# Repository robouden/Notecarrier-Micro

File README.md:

# Notecarrier-Micro

This folder contains the design files for the Blues Wireless Notecarrier-Micro, in KiCad 7 format. This is a compact carrier board designed specifically for the Blues Wireless Notecard, providing power management, interface conversion, and mechanical mounting in a minimal form factor.

The Notecarrier-Micro provides essential hardware interfaces including USB-C for programming and power, JST connectors for battery and antenna connections, and standard 0.1" headers for GPIO access. All components are selected for low power consumption and reliability in IoT applications.

## Contents

- This file
 	- `README.md`
- KiCad source files
	- `Notecarrier-Micro.kicad_pcb`
	- `Notecarrier-Micro.kicad_prl`
	- `Notecarrier-Micro.kicad_pro`
	- `Notecarrier-Micro.kicad_sch`
	- `Notecarrier-Micro.kicad_wks`
	- `sym-lib-table`
	- `fp-info-cache`	- `fp-lib-table`
- Documentation	- `documentation/*`
- Manufacturing artefacts
	- `manufacturing/*`
- Design references
	- `reference/*`
- Validation artefacts
	- `validation/*`

## Hardware Specifications

### Physical Characteristics
- **Dimensions**: Compact form factor optimized for space-constrained applications
- **Mounting**: Standard mounting holes for secure installation
- **Connectors**: USB-C, JST battery connector, antenna connectors, 0.1" GPIO headers

### Power Management
- **Input Voltage**: USB-C 5V input, Battery input via JST connector
- **Power Regulation**: On-board voltage regulators for stable 3.3V and other required voltages
- **Low Power Design**: Optimized for battery-powered IoT applications

### Interfaces
- **USB-C**: Programming, debugging, and power input
- **Battery Connector**: JST connector for LiPo battery connection
- **Antenna Connectors**: Standard antenna connections for cellular/WiFi
- **GPIO Headers**: 0.1" pitch headers for external sensor/actuator connections
- **I2C/SPI/UART**: Standard communication interfaces exposed via headers

### Compatibility
- **Notecard Support**: Designed specifically for Blues Wireless Notecard modules
- **Module Interface**: M.2 edge connector for Notecard installation
- **External Access**: All Notecard pins accessible via expansion headers

## Manufacturing Files
- **PCB Files**: Complete KiCad manufacturing package in `manufacturing/` directory
- **3D Models**: STEP and WRL files for mechanical integration
- **Assembly**: Pick and place files, BOM, and assembly drawings

## Revision History

| Revision |    Date    |   Author   | Description |
|:--------:| ---------- | ---------- | ----------- |
|     A    | 2023-03-31 | H.Raftery  | initial port from OrCAD design files, rev 14 (v2.1). |

### Original OrCad Design File Revision History

| Revision |    Date    |   Author   | Description |
|:--------:| ---------- | ---------- | ----------- |
|    12    | 25/08/2020 | G.Boschini | - Changed screw with inox version<br/>- Changed pullup resistor of EN pin to 10M |
|    14    | 25/08/2020 | M. Gregis  | - Added LiPO charger<br/>- Changed V+ to VBAT<br/>- removed BOOT signal from J21 header and replaced with GND<br/>- removed AUX5 from J22 header and replaced with VMODEM |

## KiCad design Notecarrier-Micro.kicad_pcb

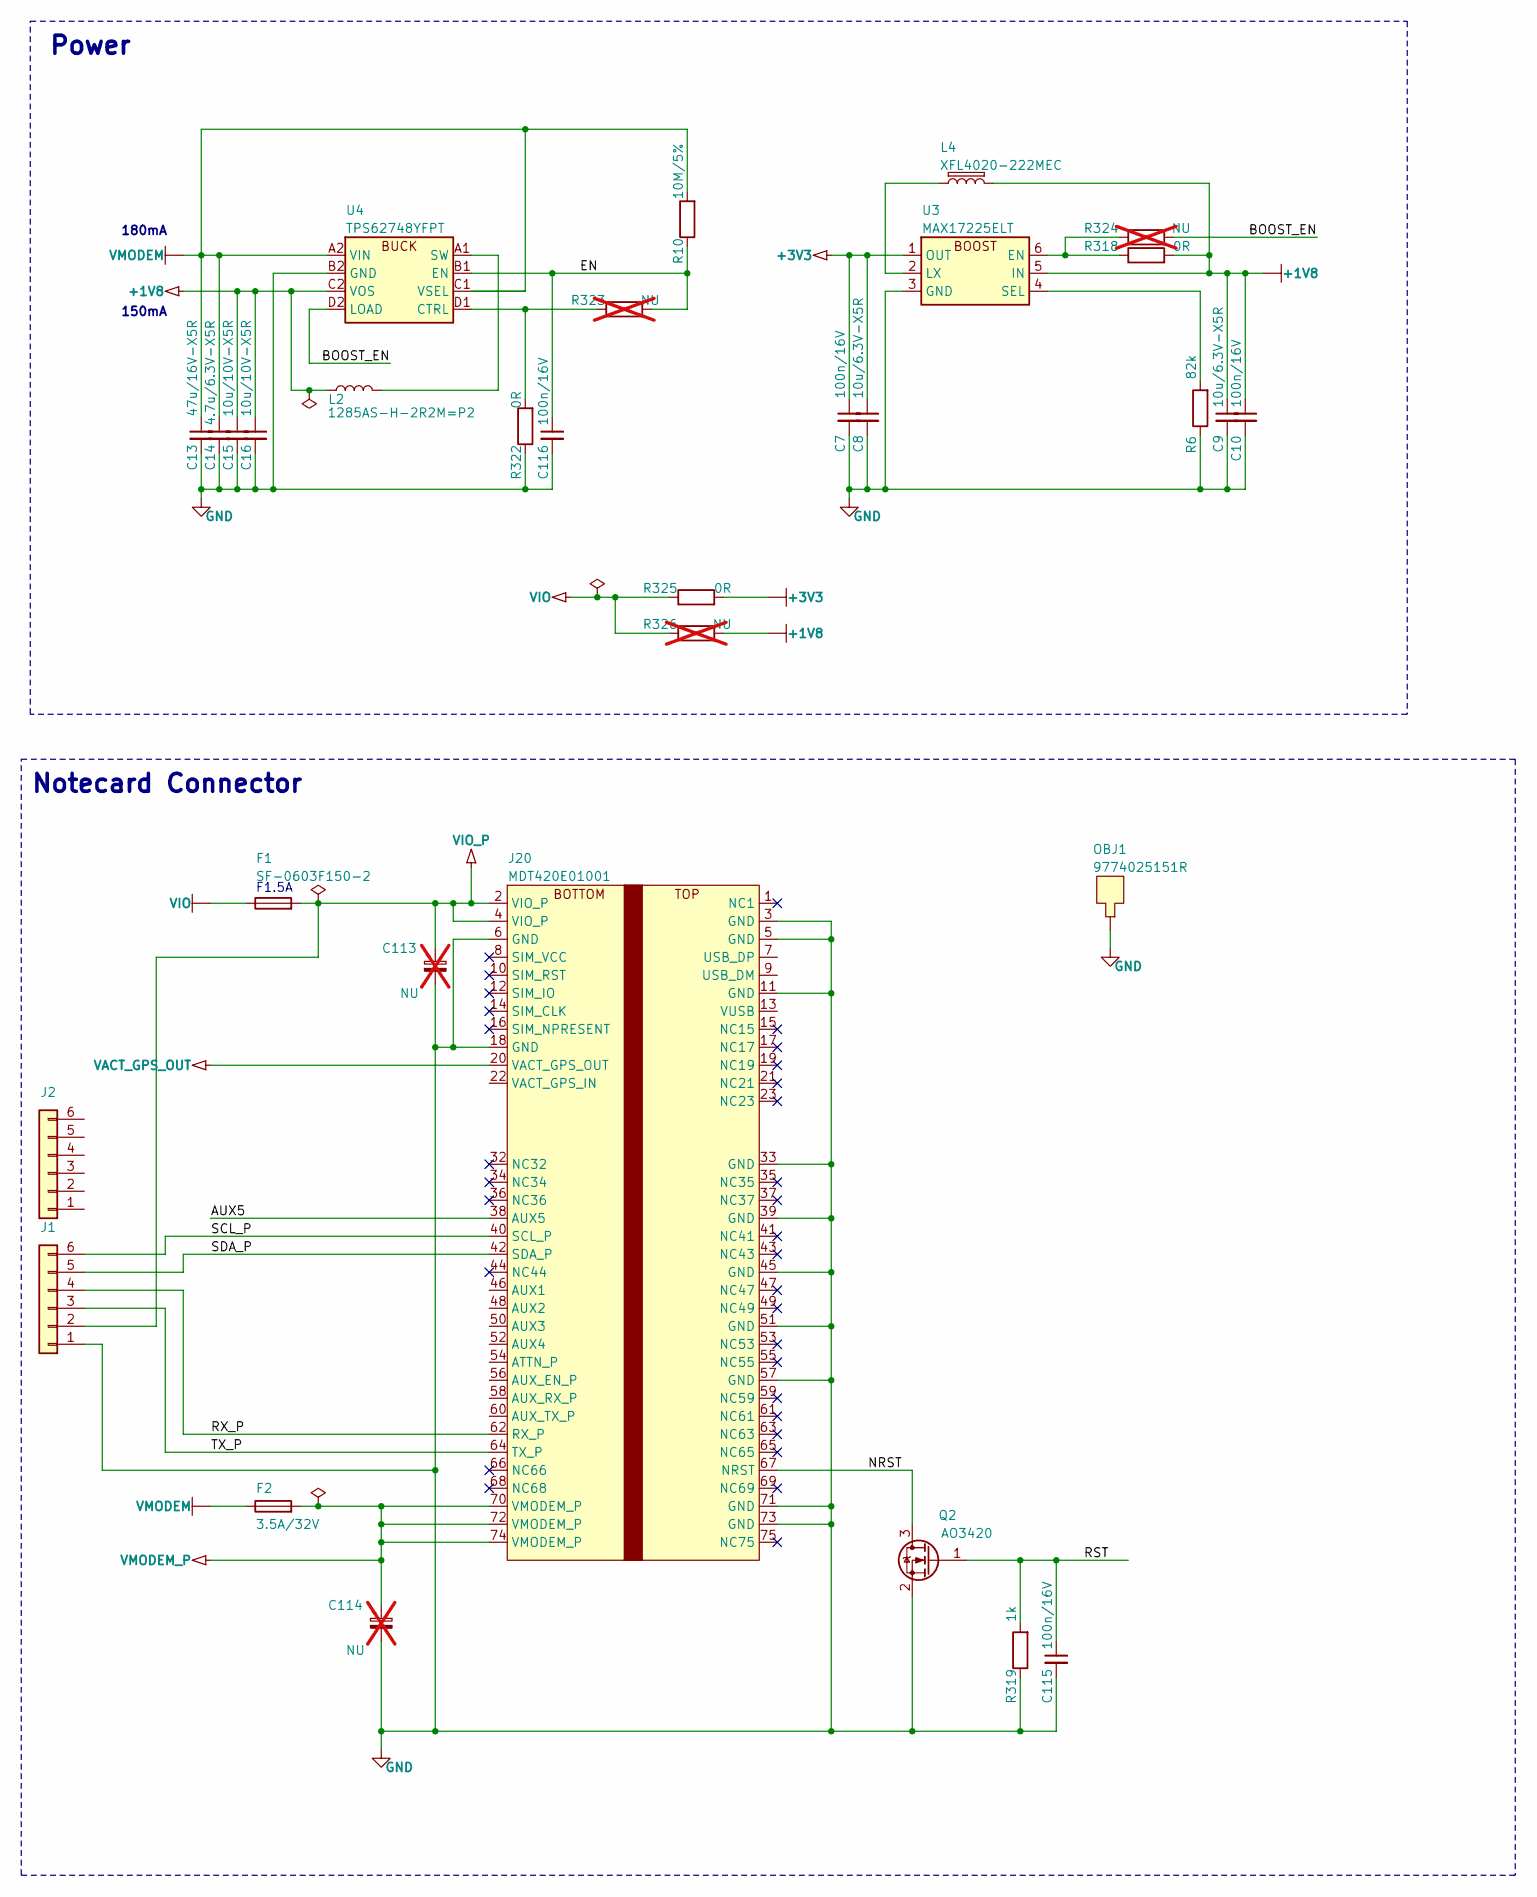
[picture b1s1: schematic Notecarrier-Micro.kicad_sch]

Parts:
C7, C10, C115, C116: 100n/16V; CS-C-0402_NO-FILL
C8, C9: 10u/6.3V-X5R; CS-C-0402_NO-FILL
C13: 47u/16V-X5R; CS-C-1206
C14: 4.7u/6.3V-X5R; CS-C-0402_NO-FILL
C15, C16: 10u/10V-X5R; CS-C-0603
C113: NU; CS-T-A; MPN F930J107KAA; not fitted
C114: NU; CS-T-B; MPN F930J227KBA; not fitted
F1: SF-0603F150-2; FS-0603; MPN SF-0603F150-2
F2: 3.5A/32V; FS-0603; MPN 0603SFV350F/32-2
J1, J2: Conn_01x06; PinHeader_1x06_P2.54mm_Vertical
J20: MDT420E01001; J-75-0050-MOS-M2-E
L2: 1285AS-H-2R2M=P2; LS-0806; MPN 1285AS-H-2R2M=P2
L4: XFL4020-222MEC; LS-XFL4020; MPN XFL4020-222MEC
OBJ1: 9774025151R; DIST-WASMSIM0250
Q2: AO3420; SOT23_NO-FILL
R6: 82k; RS-0402_NO-FILL
R10: 10M/5%; RS-0402_NO-FILL
R318, R322, R325: 0R; RS-0402_NO-FILL
R319: 1k; RS-0402_NO-FILL
R323, R324, R326: NU; RS-0402_NO-FILL; not fitted
U3: MAX17225ELT; WDFN6-0200X0200; MPN MAX17225ELT+T
U4: TPS62748YFPT; XFBGA8; MPN TPS62748YFPT

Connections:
+1V8: C9.1, C10.1, C15.1, C16.1, L2.2, L4.2, R318.2, R326.2, U3.5 (IN), U4.C2 (VOS)
+3V3: C7.1, C8.1, R325.2, U3.1 (OUT)
/AUX5: J20.38 (AUX5)
/BOOST_EN: R324.2, U4.D2 (LOAD)
/EN: C116.1, R10.1, R323.2, U4.B1 (EN)
/NRST: J20.67 (NRST), Q2.3 (D)
/RST: C115.1, Q2.1 (G), R319.2
/RX_P: J1.4, J20.62 (RX_P)
/SCL_P: J1.6, J20.40 (SCL_P)
/SDA_P: J1.5, J20.42 (SDA_P)
/TX_P: J1.3, J20.64 (TX_P)
GND: C7.2, C8.2, C9.2, C10.2, C13.2, C14.2, C15.2, C16.2, C113.2, C114.2, C115.2, C116.2, J1.1, J20.3 (GND), J20.5 (GND), J20.6 (GND), J20.11 (GND), J20.18 (GND), J20.33 (GND), J20.39 (GND), J20.45 (GND), J20.51 (GND), J20.57 (GND), J20.71 (GND), J20.73 (GND), OBJ1.1, Q2.2 (S), R6.1, R319.1, R322.1, U3.3 (GND), U4.B2 (GND)
unnamed: R318.1, R324.1, U3.6 (EN)
unnamed: L4.1, U3.2 (LX)
unnamed: R6.2, U3.4 (SEL)
unnamed: R322.2, R323.1, U4.D1 (CTRL)
unnamed: L2.1, U4.A1 (SW)
VACT_GPS_OUT: J20.20 (VACT_GPS_OUT)
VIO: F1.1, R325.1, R326.1
VIO_P: C113.1, F1.2, J1.2, J20.2 (VIO_P), J20.4 (VIO_P)
VMODEM: C13.1, C14.1, F2.1, R10.2, U4.A2 (VIN), U4.C1 (VSEL)
VMODEM_P: C114.1, F2.2, J20.70 (VMODEM_P), J20.72 (VMODEM_P), J20.74 (VMODEM_P)

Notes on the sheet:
150mA
180mA
F1.5A
Notecard Connector
Power

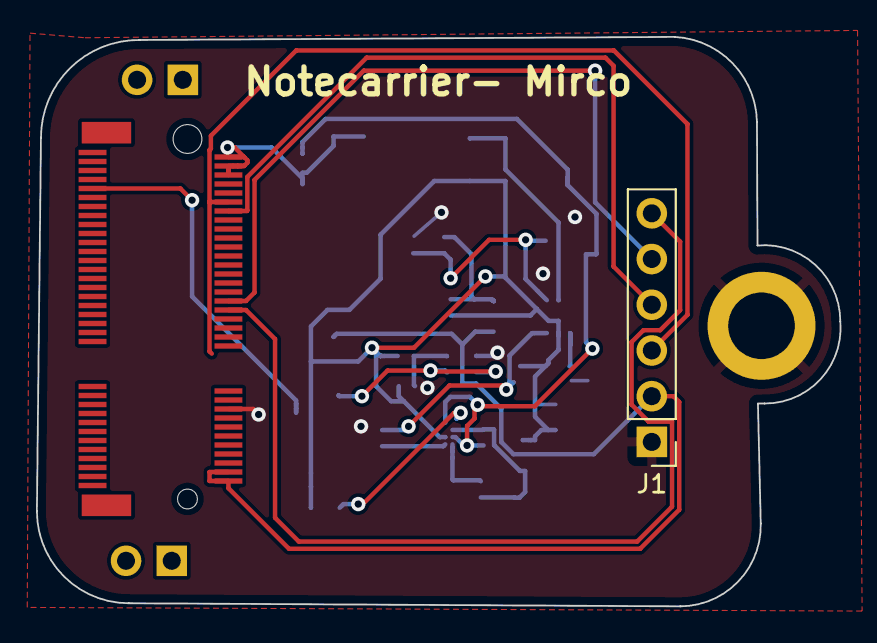
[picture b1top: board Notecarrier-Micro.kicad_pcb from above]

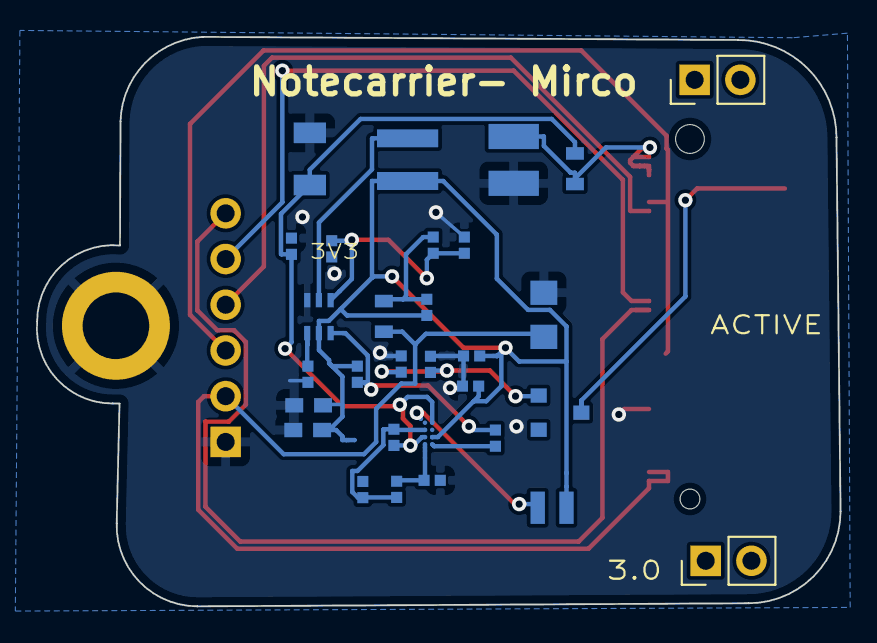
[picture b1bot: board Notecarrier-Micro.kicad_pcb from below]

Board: 2 copper layers, 44.6 x 31.6 mm, 33 parts (30 on the bottom side), 20 nets.

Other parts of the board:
Extra_pin_1, Extra_pin_2: PinHeader_1x02_P2.54mm_Vertical

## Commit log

2025-07-22 Init
2025-07-24 Small fixes 3D notecard fill
2025-07-24 Added 3d model M2 connector
2025-07-24 update the readme.md file

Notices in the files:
Notecarrier-Micro.kicad_pcb:
Blues Inc (Copyright (c) 2023 Blues Inc)
